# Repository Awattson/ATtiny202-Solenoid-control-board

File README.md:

📘 [日本語 README](README.md) | [English README](README.en.md)

# ATtiny202 Solenoid Control Board

ATtiny202を使用してソレノイドを3つ制御するための小型マイコンボードです。

---

## 📌 概要

このボードは、USART経由で3つのソレノイドを個別にON/OFF制御するために設計されています。  
シリアル通信で受け取った1文字のcharデータ（'0'〜'7'）を3ビットのON/OFF信号として扱い、それに応じてソレノイドを駆動します。

例：
- `'0'` → `0b000` → 全ソレノイドOFF
- `'2'` → `0b010` → 真ん中のソレノイドON、それ以外OFF
- `'7'` → `0b111` → 全ソレノイドON

---

## 🧩 特徴・構成

- **メインチップ**：ATtiny202
- **入力電源**：XT30PW-M コネクタから 18V〜26V を入力
- **電源回路**：BP5293-50 により 5V に降圧
- **ロジック電圧**：3.3V
- **インターフェース**：
  - USART（シリアル通信）
  - UPDI（プログラミング用）
- **出力素子**：2SK4017（Nch MOSFET）
- **絶縁**：TLP291（フォトカプラ）
- **制御方法**：USARTからchar入力によるソレノイドON/OFF制御
- **開発環境**：Arduino（ATtiny202用）

---

## 🛠 使用部品

| 部品名       | 備考               |
|--------------|--------------------|
| ATtiny202    | メインマイコン     |
| 2SK4017      | ソレノイド駆動用MOSFET |
| TLP291       | 信号絶縁用フォトカプラ |
| BP5293-50    | DC-DCコンバータ（18–26V→5V） |
| XHコネクタ   | ソレノイド出力用     |
| XT30PW-M     | 電源入力用コネクタ   |

---

## 🧾 製造について

- **製造業者**：JLCPCB で製造可能（2層基板）
- **部品調達**：すべて秋月電子通商で購入可能
- **実装**：手はんだ対応設計、両面実装あり

---

## 📄 ライセンス

本プロジェクトは [MITライセンス](LICENSE) に基づいて公開されています。

自由にご利用・改変・再配布いただけますが、著作権表示とライセンス文は残してください。

---

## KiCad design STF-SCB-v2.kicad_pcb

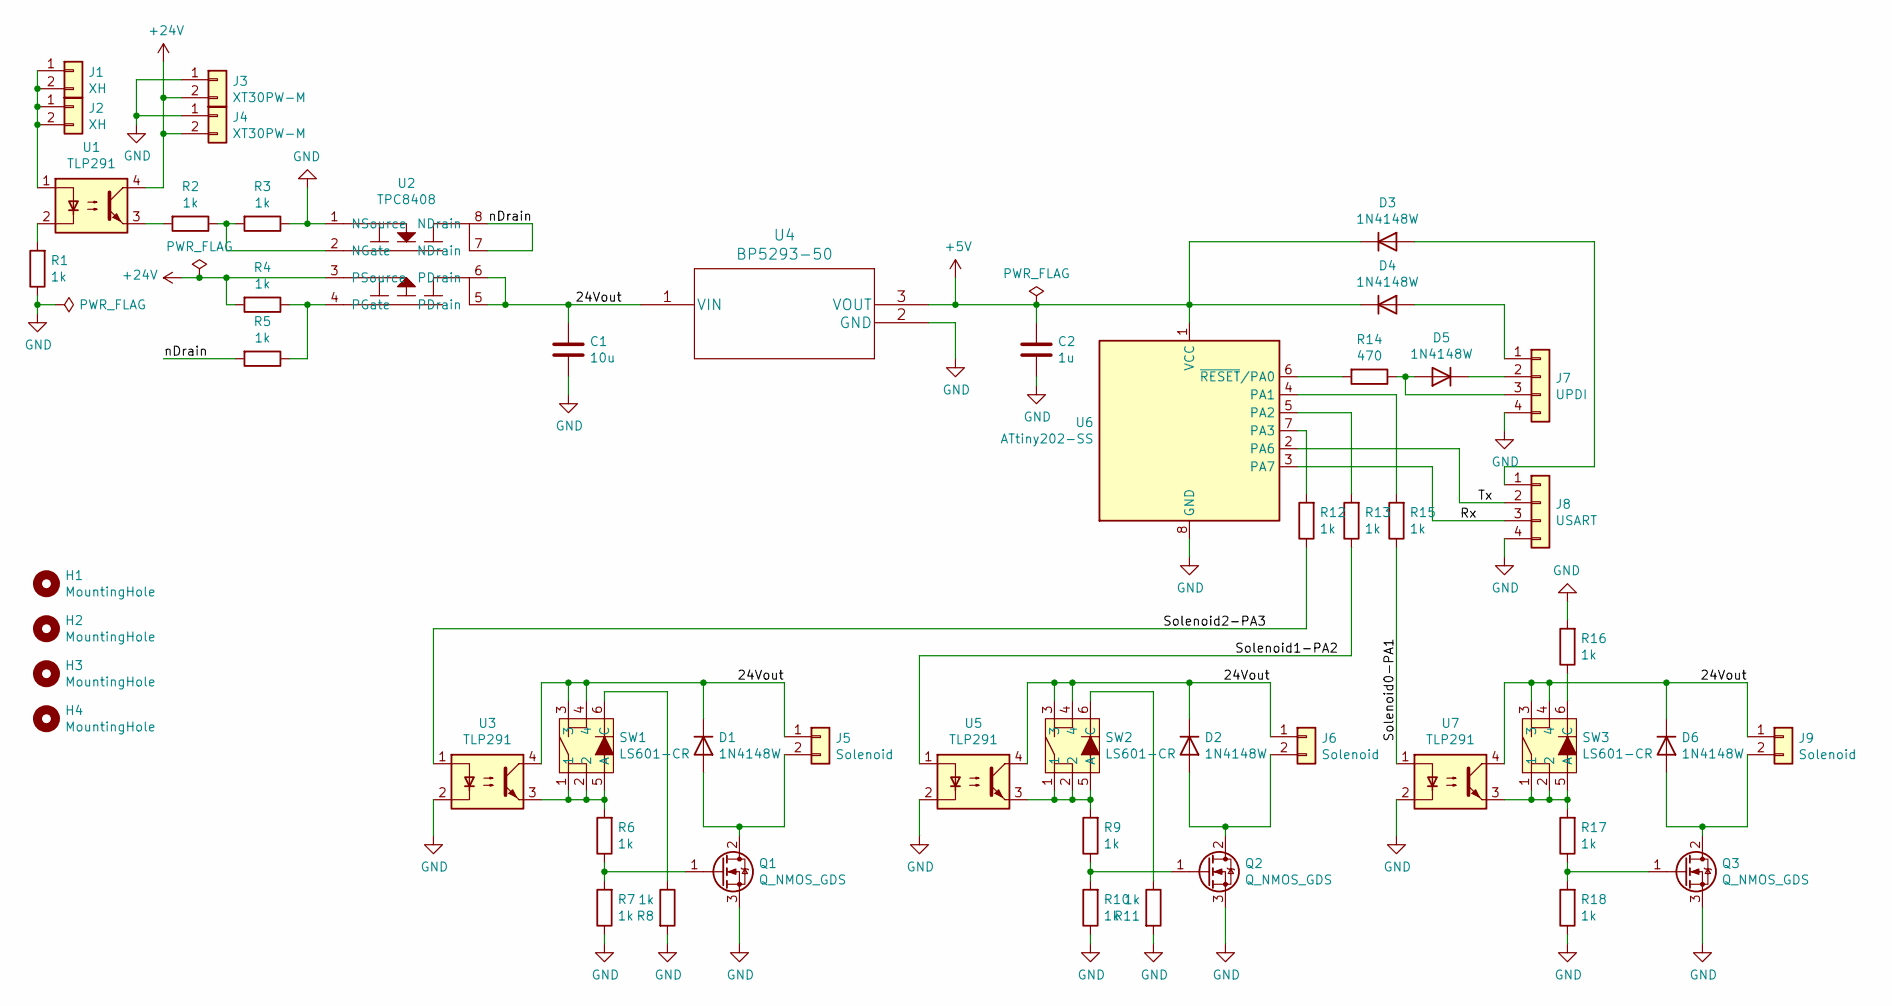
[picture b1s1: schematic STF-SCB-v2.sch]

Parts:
C1: 10u; C_1206_3216Metric
C2: 1u; C_1206_3216Metric
D1, D2, D3, D4, D5, D6: 1N4148W; D_SOD-123
H1, H2, H3, H4: MountingHole; MountingHole_3.2mm_M3
J1, J2: XH; JST_XH_B2B-XH-A_1x02_P2.50mm_Vertical
J3, J4: XT30PW-M; AMASS_XT30PW-M_1x02_P2.50mm_Horizontal
J5, J6, J9: Solenoid; JST_XH_B2B-XH-A_1x02_P2.50mm_Vertical
J7: UPDI; JST_XH_B4B-XH-A_1x04_P2.50mm_Vertical
J8: USART; JST_XH_B4B-XH-A_1x04_P2.50mm_Vertical
Q1, Q2, Q3: Q_NMOS_GDS; TO-251-3_Vertical
R1, R2, R3, R4, R5, R6, R7, R8, R9, R10, R11, R12, R13, R15, R16, R17, R18: 1k; R_1206_3216Metric
R14: 470; R_1206_3216Metric
SW1, SW2, SW3: LS601-CR
U1, U3, U5, U7: TLP291; SOIC-4_4.55x2.6mm_P1.27mm
U2: TPC8408; SOP-8_3.9x4.9mm_P1.27mm
U4: BP5293-50
U6: ATtiny202-SS; SOIC-8_3.9x4.9mm_P1.27mm

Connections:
+5V: C2.1, D3.1 (K), D4.1 (K), U4.3 (VOUT), U6.1 (VCC)
+24V: J3.2, J4.2, R4.2, U1.4, U2.3 (PSource)
/24Vout: C1.1, D1.1 (K), D2.1 (K), D6.1 (K), J5.1, J6.1, J9.1, SW1.3, SW1.4, SW2.3, SW2.4, SW3.3, SW3.4, U2.5 (PDrain), U2.6 (PDrain), U3.4, U4.1 (VIN), U5.4, U7.4
/Rx: J8.3, U6.3 (PA7)
/Solenoid0-PA1: R15.1, U7.1
/Solenoid1-PA2: R13.1, U5.1
/Solenoid2-PA3: R12.1, U3.1
/Tx: J8.2, U6.2 (PA6)
/nDrain: R5.2, U2.7 (NDrain), U2.8 (NDrain)
GND: C1.2, C2.2, J3.1, J4.1, J7.4, J8.4, Q1.3 (S), Q2.3 (S), Q3.3 (S), R1.1, R3.1, R7.1, R8.2, R10.1, R11.2, R16.2, R18.1, U2.1 (NSource), U3.2, U4.2 (GND), U5.2, U6.8 (GND), U7.2
unnamed: D1.2 (A), J5.2, Q1.2 (D)
unnamed: D2.2 (A), J6.2, Q2.2 (D)
unnamed: D3.2 (A), J8.1
unnamed: D4.2 (A), J7.1
unnamed: D5.1 (K), J7.2
unnamed: D5.2 (A), J7.3, R14.1
unnamed: D6.2 (A), J9.2, Q3.2 (D)
unnamed: J1.1, J1.2, J2.1, J2.2, U1.1
unnamed: Q1.1 (G), R6.1, R7.2
unnamed: Q2.1 (G), R9.1, R10.2
unnamed: Q3.1 (G), R17.1, R18.2
unnamed: R1.2, U1.2
unnamed: R2.1, R3.2, U2.2 (NGate)
unnamed: R2.2, U1.3
unnamed: R4.1, R5.1, U2.4 (PGate)
unnamed: R6.2, SW1.1, SW1.2, SW1.5 (A), U3.3
unnamed: R8.1, SW1.6 (C)
unnamed: R9.2, SW2.1, SW2.2, SW2.5 (A), U5.3
unnamed: R11.1, SW2.6 (C)
unnamed: R12.2, U6.7 (PA3)
unnamed: R13.2, U6.5 (PA2)
unnamed: R14.2, U6.6 (~RESET~/PA0)
unnamed: R15.2, U6.4 (PA1)
unnamed: R16.1, SW3.6 (C)
unnamed: R17.2, SW3.1, SW3.2, SW3.5 (A), U7.3

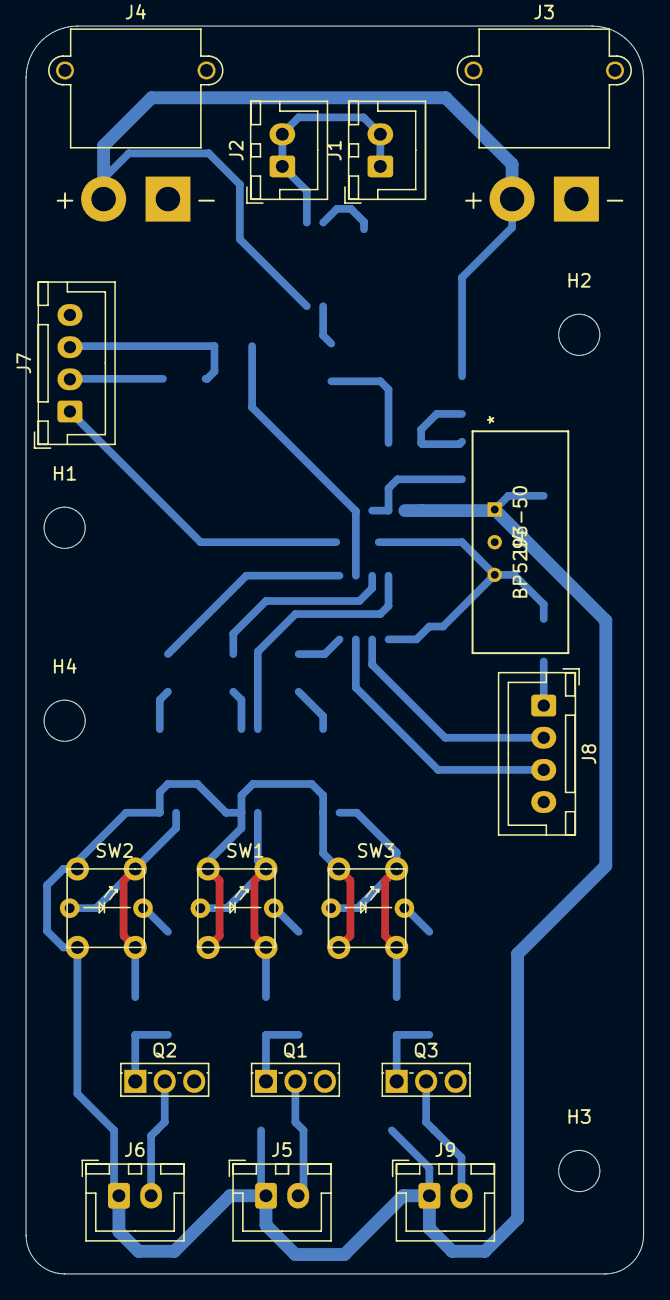
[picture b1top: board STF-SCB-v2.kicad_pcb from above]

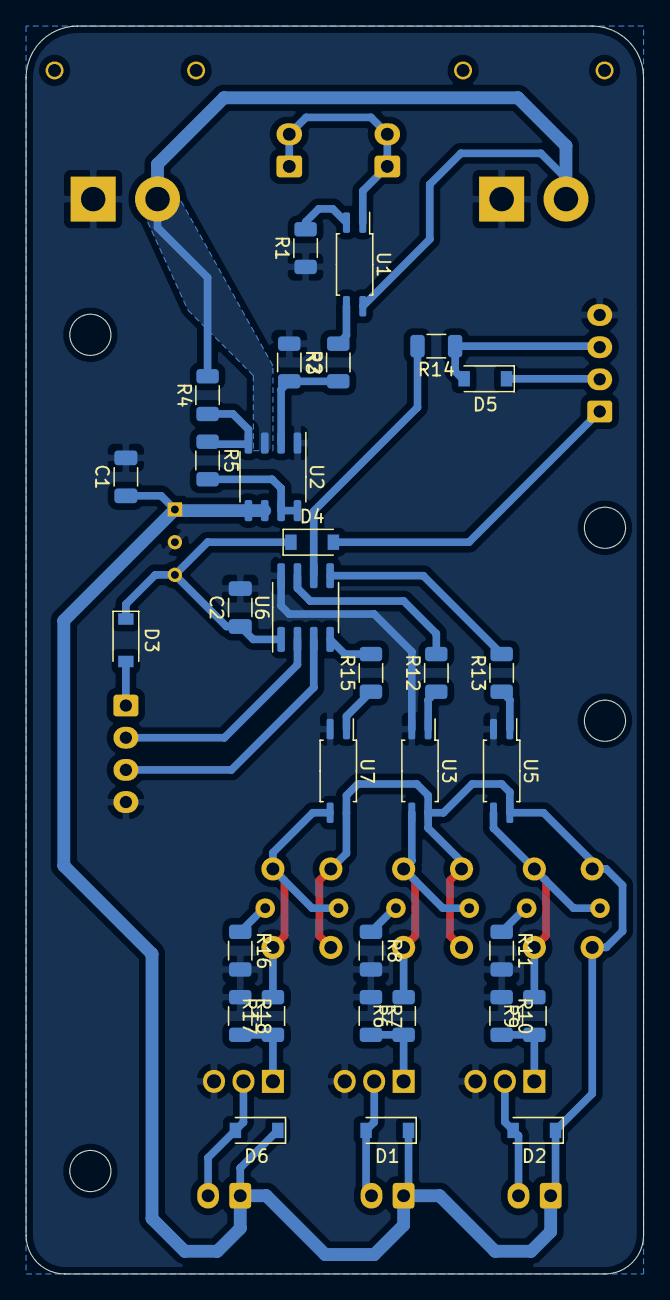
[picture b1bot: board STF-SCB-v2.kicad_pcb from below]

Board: 2 copper layers, 48.0 x 97.0 mm, 52 parts (32 on the bottom side), 35 nets.

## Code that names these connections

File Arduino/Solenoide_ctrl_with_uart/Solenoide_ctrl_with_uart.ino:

void setup() {
  // put your setup code here, to run once:
  pinMode(PIN_PA1, OUTPUT);
  pinMode(PIN_PA2, OUTPUT);
  pinMode(PIN_PA6, OUTPUT);
  pinMode(PIN_PA7, OUTPUT);

  digitalWrite(PIN_PA1, LOW);
  digitalWrite(PIN_PA2, LOW);
  digitalWrite(PIN_PA6, LOW);
  digitalWrite(PIN_PA7, LOW);
  delay(100);
  //Serial.begin(9600);
}

void loop() {
  // put your main code here, to run repeatedly:
  static bool s0 = false;
  static bool s1 = false;
  /*
  if(Serial.available()){
    
    int buf = Serial.read();
    bool state0 = (buf >> 3) & 0x01;
    bool state1 = (buf >> 2) & 0x01;
    bool state2 = (buf >> 1) & 0x01;
    bool state3 = buf & 0x01;

    digitalWrite(PIN_PA1, state0);
    digitalWrite(PIN_PA2, state1);
    digitalWrite(PIN_PA6, state2);
    digitalWrite(PIN_PA7, state3);
    
    char c = Serial.read();
    switch(c){
      case '1':
        digitalWrite(PIN_PA6, s0);
        s0 = !s0;
        break;
      case '2':
        digitalWrite(PIN_PA7, s1);
        s1 = !s1;
        break;
      
    }

    delay(10);
  }*/
  digitalWrite(PIN_PA6, s0);
  digitalWrite(PIN_PA7, s1);
  delay(1000);
  s0 = !s0;
  s1 = !s1;
}

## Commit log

2025-05-12 2025-05-12
2025-05-12 2025-05-12-12:55
2025-05-12 add two readme files

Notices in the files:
parts and their libraries:
Copyright 2016 Accelerated Designs. All rights reserved.
